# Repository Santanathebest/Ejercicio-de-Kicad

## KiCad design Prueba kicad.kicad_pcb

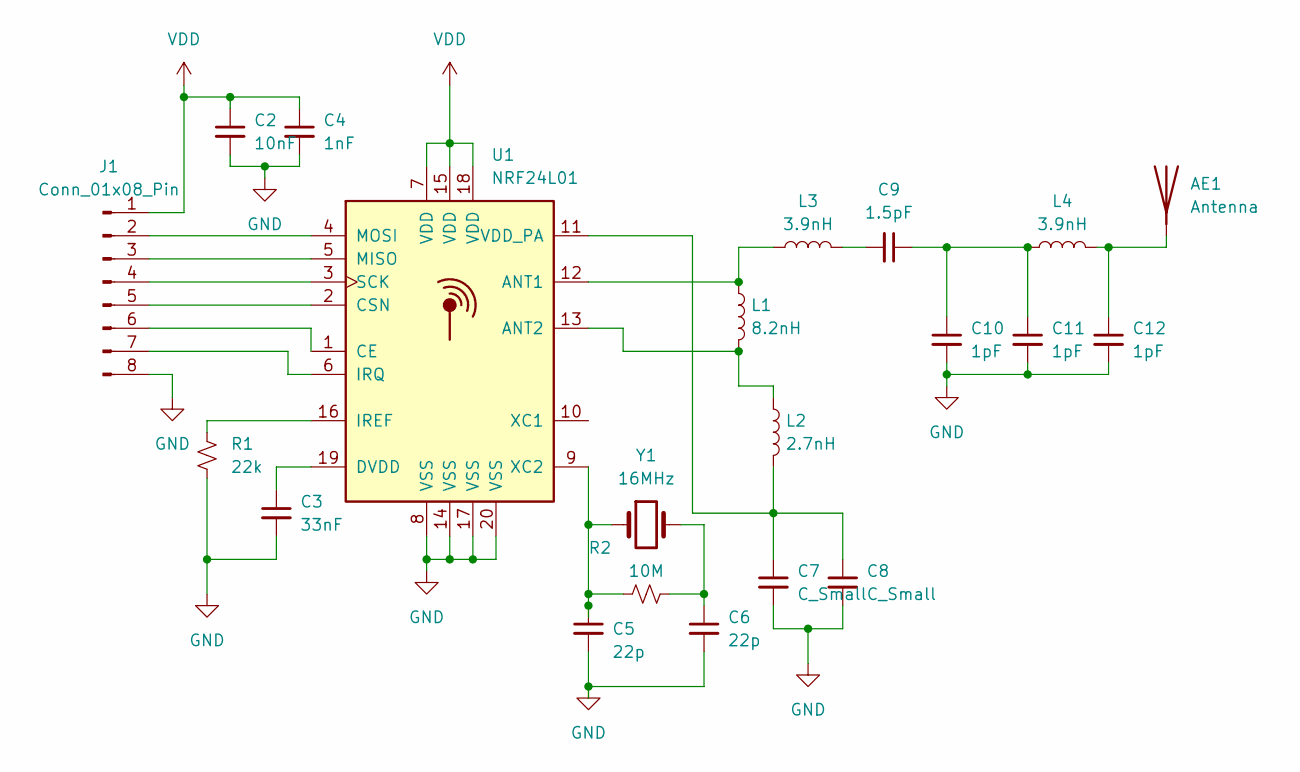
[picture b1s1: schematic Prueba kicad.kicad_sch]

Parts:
AE1: Antenna; Texas_SWRA117D_2.4GHz_Right
C2: 10nF; C_0402_1005Metric
C3: 33nF; C_0402_1005Metric
C4: 1nF; C_0402_1005Metric
C5, C6: 22p; C_0402_1005Metric
C7, C8: C_Small; C_0402_1005Metric
C9: 1.5pF; C_0402_1005Metric
C10, C11, C12: 1pF; C_0402_1005Metric
J1: Conn_01x08_Pin; Hirose_DF13-08P-1.25DSA_1x08_P1.25mm_Vertical
L1: 8.2nH; L_0402_1005Metric
L2: 2.7nH; L_0402_1005Metric
L3, L4: 3.9nH; L_0402_1005Metric
R1: 22k; R_0402_1005Metric
R2: 10M; R_0402_1005Metric
U1: NRF24L01; QFN-20-1EP_4x4mm_P0.5mm_EP2.5x2.5mm
Y1: 16MHz; Crystal_SMD_3215-2Pin_3.2x1.5mm

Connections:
GND: C2.2, C3.2, C4.2, C5.2, C6.2, C7.2, C8.2, C10.2, C11.2, C12.2, J1.8, R1.2, U1.8 (VSS), U1.14 (VSS), U1.17 (VSS), U1.20 (VSS)
unnamed: AE1.1 (A), C12.1, L4.2
unnamed: C6.1, R2.2, Y1.2
unnamed: C9.2, L3.2
unnamed: C9.1, C10.1, C11.1, L4.1
unnamed: J1.2, U1.4 (MOSI)
unnamed: J1.3, U1.5 (MISO)
unnamed: J1.4, U1.3 (SCK)
unnamed: J1.5, U1.2 (CSN)
unnamed: J1.6, U1.1 (CE)
unnamed: J1.7, U1.6 (IRQ)
unnamed: L1.1, L3.1, U1.12 (ANT1)
unnamed: L1.2, L2.1, U1.13 (ANT2)
unnamed: C3.1, U1.19 (DVDD)
unnamed: R1.1, U1.16 (IREF)
unnamed: C7.1, C8.1, L2.2, U1.11 (VDD_PA)
unnamed: C5.1, R2.1, U1.9 (XC2), Y1.1
VDD: C2.1, C4.1, J1.1, U1.7 (VDD), U1.15 (VDD), U1.18 (VDD)

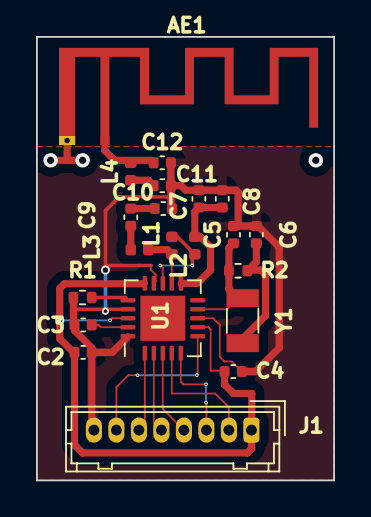
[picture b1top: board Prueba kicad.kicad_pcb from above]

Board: 2 copper layers, 16.5 x 24.6 mm, 21 parts (0 on the bottom side), 18 nets.

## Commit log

2024-06-05 listo
